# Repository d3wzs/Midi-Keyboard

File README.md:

# Midi-Keyboard

Midi Keyboard is a variation of Half Lifes Midi Keyboard (Week 3) Project. I've edited to have a better layout in my opinion. Ive added my own star design from my previous week 1 project.

The board features 3 low profile buttons, a 2 pentiometers, a rotary encoder and a Waveshare ESP32-S3-Zero as the main controller. The board has Capacitive keys aswell. 

# Features/Attributes

-Custom PCB
-Capacitive Keys
-Sliders
-Star Design
-Buttons
-Rotary Encoders
-Led lighting

# Hardware

-Waveshare ESP32-S3-Zero: Micro-controller
-PCB
-Potentiometer Bourns PTA1543: Interaction
-LED SK6812MINI-E 3.2x2.8mm Reverse Mount: Lighting
-Kailh Choc Low-Profile Switches: Interaction
-Rotary Encoder Alps EC11E H20mm: Interaction

# Repository Guide

-BOM.csv: Bill of Materials
-Journal.MD: Journal Entries
-MIDI-Gerber.zip: Project Gerber File
-MIDI.kicad_pcb: PCB File
-MIDI.kicad_sch: Schematic File
-README.md: Read me

# Bill of Materials

|Item                    |Qty|Supplier  |Cost/item|Total Cost|link                                                                                                                                                                                                                                                                                                                                                                                                                                                                                                                                                                                                                                      |
|------------------------|---|----------|---------|----------|------------------------------------------------------------------------------------------------------------------------------------------------------------------------------------------------------------------------------------------------------------------------------------------------------------------------------------------------------------------------------------------------------------------------------------------------------------------------------------------------------------------------------------------------------------------------------------------------------------------------------------------|
|ESP32-S3-Zero mini      |1  |Aliexpress|$6.68    |$6.68     |https://www.aliexpress.com/item/1005007004089798.html?src=google&gatewayAdapt=4itemAdapt                                                                                                                                                                                                                                                                                                                                                                                                                                                                                                                                                  |
|Bourns Pontetiometer    |2  |Digikey   |$1.84    |$3.68     |https://www.digikey.com/en/products/detail/bourns-inc/PTA1543-2010CIB103/3781161                                                                                                                                                                                                                                                                                                                                                                                                                                                                                                                                                          |
|Kailh Choc Switches     |1  |Aliexpress|$4.31    |$4.31     |https://www.aliexpress.com/item/1005012098783556.html?spm=a2g0o.productlist.main.3.402c3c5fE10JnJ&algo_pvid=9d31b5cf-3eee-43b0-bbc1-46d8f199b5d5&algo_exp_id=9d31b5cf-3eee-43b0-bbc1-46d8f199b5d5-37&pdp_ext_f=%7B%22order%22%3A%226%22%2C%22eval%22%3A%221%22%2C%22fromPage%22%3A%22search%22%7D&pdp_npi=6%40dis%21USD%214.31%214.31%21%21%2128.65%2128.65%21%4021030f8317924203622946649e0f45%2112000057508619516%21sea%21CA%217748192322%21X%211%210%21n_tag%3A-29919%3Bd%3Aa40d61bf%3Bm03_new_user%3A-29895&curPageLogUid=NXh9kZBiprvA&utparam-url=scene%3Asearch%7Cquery_from%3A%7Cx_object_id%3A1005012098783556%7C_p_origin_prod%3A|
|Rotary Encoder          |1  |Aliexpress|$2.63    |$2.63     |https://www.aliexpress.com/item/1005007644083514.html?gatewayAdapt=usa2glo4itemAdapt                                                                                                                                                                                                                                                                                                                                                                                                                                                                                                                                                      |
|SK6812MINI-E            |1  |Aliexpress|$4.56    |$4.56     |https://www.aliexpress.com/item/1005007863635868.html?spm=a2g0o.productlist.0.0.18f51c3co9Z6x6&mp=1&pdp_npi=6%40dis%21USD%21USD+4.57%21USD+4.57%21%21USD+4.57%21%21%21%40210327ef17924207860181186e0e85%2112000042594617264%21ct%21CA%217748192322%21%211%210%21                                                                                                                                                                                                                                                                                                                                                                          |
|PCB                     |1  |JLCPCB    |$8.60    |$8.60     |https://cart.jlcpcb.com/quote?stencilLayer=2&stencilWidth=100&stencilLength=100&stencilCounts=5&plateType=1&spm=Jlcpcb.Homepage.1010                                                                                                                                                                                                                                                                                                                                                                                                                                                                                                      |
|Estimated total shipping|1  |          |         |$2.62     |                                                                                                                                                                                                                                                                                                                                                                                                                                                                                                                                                                                                                                          |

# Media

# Author

All of this is thanks to half life by hack club. Big thanks to them
-d3wzs(d3wzy)

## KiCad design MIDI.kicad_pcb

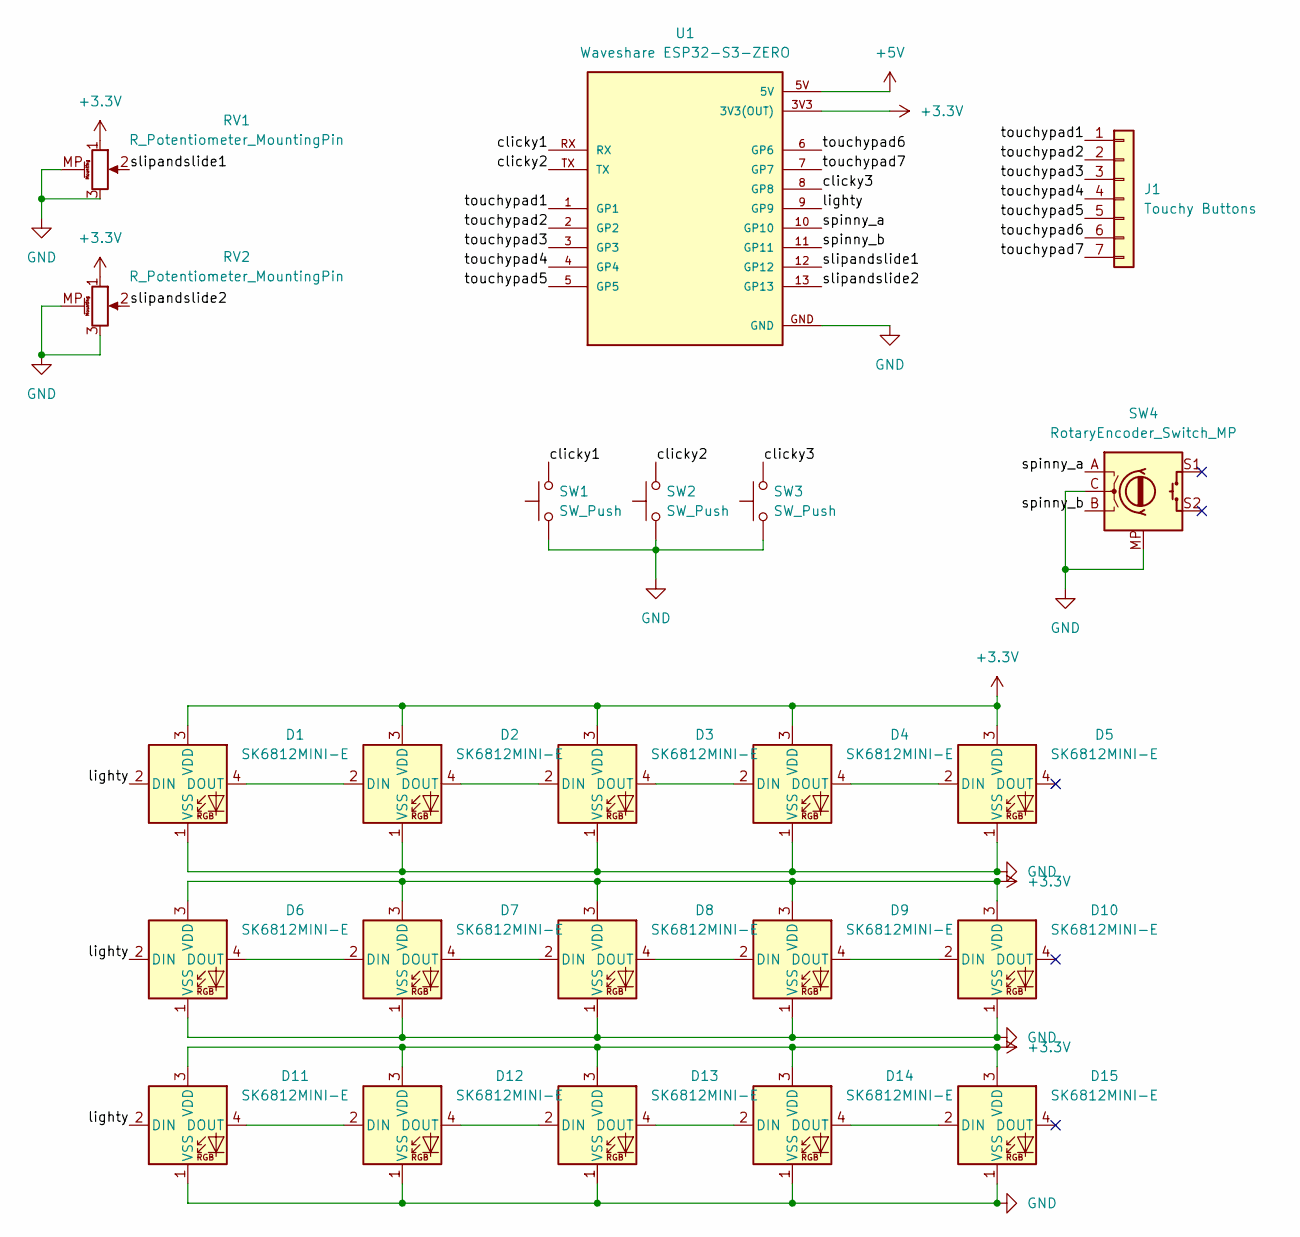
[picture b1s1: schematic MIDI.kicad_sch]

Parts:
D1, D2, D3, D4, D5, D6, D7, D8, D9, D10, D11, D12, D13, D14, D15: SK6812MINI-E; LED_SK6812MINI-E_3.2x2.8mm_P1.5mm_ReverseMount
J1: Touchy Buttons; capacitive keys
RV1, RV2: R_Potentiometer_MountingPin; Potentiometer_Bourns_PTA1543_Single_Slide
SW1, SW2, SW3: SW_Push; Kailh Choc Low-Profile Switches
SW4: RotaryEncoder_Switch_MP; RotaryEncoder_Alps_EC11E-Switch_Vertical_H20mm
U1: Waveshare ESP32-S3-ZERO; Waveshare ESP32-S3-Zero; PARTREV NA

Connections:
+3.3V: D1.3 (VDD), D2.3 (VDD), D3.3 (VDD), D4.3 (VDD), D5.3 (VDD), D6.3 (VDD), D7.3 (VDD), D8.3 (VDD), D9.3 (VDD), D10.3 (VDD), D11.3 (VDD), D12.3 (VDD), D13.3 (VDD), D14.3 (VDD), D15.3 (VDD), RV1.1, RV2.1, U1.3V3 (3V3(OUT))
+5V: U1.5V
/clicky1: SW1.2, U1.RX
/clicky2: SW2.2, U1.TX
/clicky3: SW3.2, U1.8 (GP8)
/lighty: D1.2 (DIN), D6.2 (DIN), D11.2 (DIN), U1.9 (GP9)
/slipandslide1: RV1.2, U1.12 (GP12)
/slipandslide2: RV2.2, U1.13 (GP13)
/spinny_a: SW4.A, U1.10 (GP10)
/spinny_b: SW4.B, U1.11 (GP11)
/touchypad1: J1.1, U1.1 (GP1)
/touchypad2: J1.2, U1.2 (GP2)
/touchypad3: J1.3, U1.3 (GP3)
/touchypad4: J1.4, U1.4 (GP4)
/touchypad5: J1.5, U1.5 (GP5)
/touchypad6: J1.6, U1.6 (GP6)
/touchypad7: J1.7, U1.7 (GP7)
GND: D1.1 (VSS), D2.1 (VSS), D3.1 (VSS), D4.1 (VSS), D5.1 (VSS), D6.1 (VSS), D7.1 (VSS), D8.1 (VSS), D9.1 (VSS), D10.1 (VSS), D11.1 (VSS), D12.1 (VSS), D13.1 (VSS), D14.1 (VSS), D15.1 (VSS), RV1.3, RV1.MP (MountPin), RV2.3, RV2.MP (MountPin), SW1.1, SW2.1, SW3.1, SW4.C, SW4.MP, U1.GND
unnamed: D1.4 (DOUT), D2.2 (DIN)
unnamed: D2.4 (DOUT), D3.2 (DIN)
unnamed: D3.4 (DOUT), D4.2 (DIN)
unnamed: D4.4 (DOUT), D5.2 (DIN)
unnamed: D6.4 (DOUT), D7.2 (DIN)
unnamed: D7.4 (DOUT), D8.2 (DIN)
unnamed: D8.4 (DOUT), D9.2 (DIN)
unnamed: D9.4 (DOUT), D10.2 (DIN)
unnamed: D11.4 (DOUT), D12.2 (DIN)
unnamed: D12.4 (DOUT), D13.2 (DIN)
unnamed: D13.4 (DOUT), D14.2 (DIN)
unnamed: D14.4 (DOUT), D15.2 (DIN)

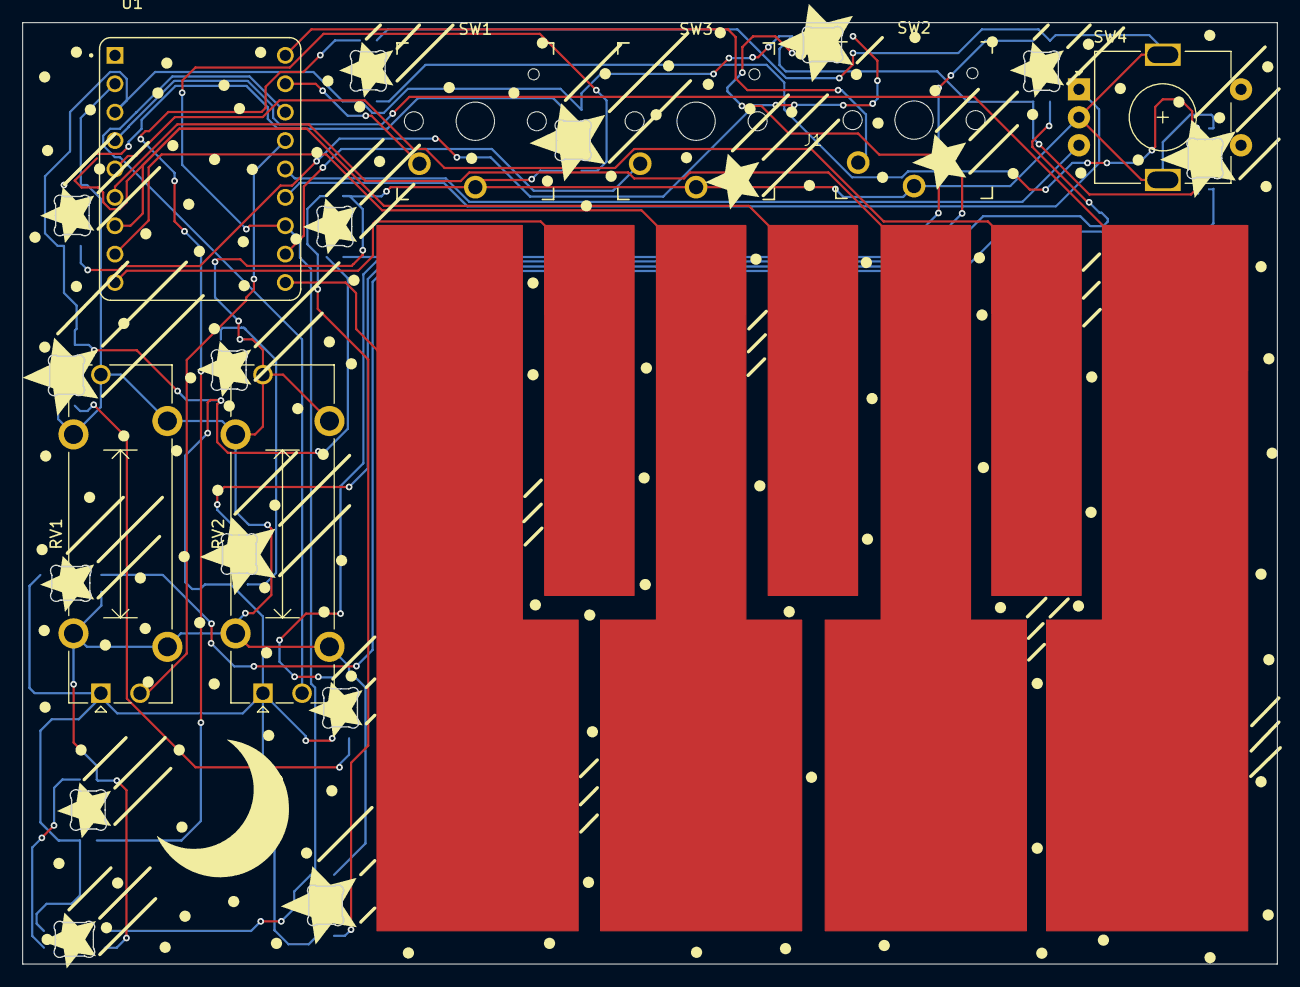
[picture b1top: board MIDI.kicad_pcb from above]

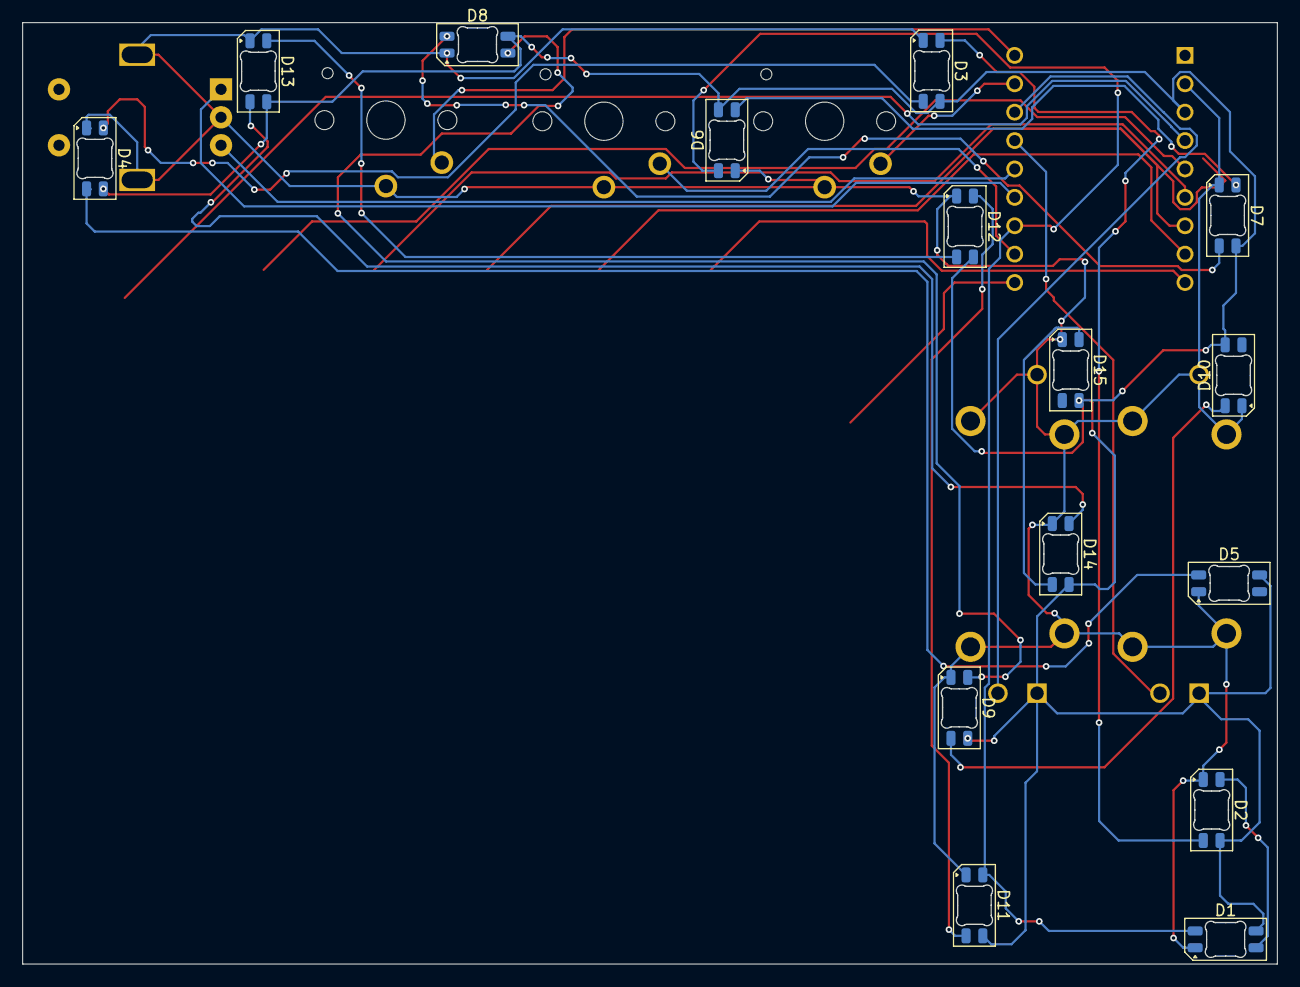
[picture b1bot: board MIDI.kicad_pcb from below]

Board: 2 copper layers, 112.2 x 84.2 mm, 23 parts (15 on the bottom side), 29 nets.
